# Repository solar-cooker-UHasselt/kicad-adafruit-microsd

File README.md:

# kicad-adafruit-microsd

A breakout board for a microSD card over SPI. It has a push-push socket with card
detect, an activity LED, a 3.3 V regulator for the card and a 74HC4050 level shifter so
it works with 3.3 V and 5 V boards. It is a KiCad 10 port of
[Adafruit's microSD breakout](https://github.com/adafruit/MicroSD-breakout-board),
originally drawn in Eagle.

In the [solar cooker](https://github.com/solar-cooker-UHasselt) testing station, the
firmware ([arduino-code](https://github.com/solar-cooker-UHasselt/arduino-code))
writes every measurement to CSV files on the card over SPI.

- [Board page](https://solar-cooker-uhasselt.github.io/kicad-adafruit-microsd/): 3D
  renders, drawings, schematic and board PDF, interactive BOM and the BOM CSV for
  Eurocircuits, rebuilt by CI on every push to `main`
- [PCB source](https://github.com/adafruit/MicroSD-breakout-board): Adafruit's Eagle
  files
- [Adafruit guide](https://learn.adafruit.com/adafruit-micro-sd-breakout-board-card-tutorial):
  pinout, wiring, card formatting and Arduino examples

## Installation

### Requirements

- [KiCad 10](https://www.kicad.org/download/), to open and edit the board
- [git](https://git-scm.com), to clone the repo
- Optional, for the checks: [just](https://just.systems)

### Clone

```bash
git clone https://github.com/solar-cooker-UHasselt/kicad-adafruit-microsd.git
```

Own symbols, footprints and 3D models are in `external/`, in the repo itself.

## Usage

Open `microSD.kicad_pro` in KiCad 10. The schematic and board open from there.

Before committing, run ERC and DRC, reports in `tmp/`:

```bash
just check
```

`just --list` shows the other recipes: PDFs, and the CI workflow run locally.

## Contributing

- Work on a branch and open a pull request to `main`. It merges once CI passes and a code
  owner (listed in [.github/CODEOWNERS](.github/CODEOWNERS)) approves it. `main`
  accepts no force pushes.
- CI runs ERC and DRC on every pull request, through the shared workflows in
  [kicad-ci](https://github.com/solar-cooker-UHasselt/kicad-ci). `just check` runs the
  same check locally. A push to `main` that changes more than Markdown also rebuilds
  the board page.
- Commits follow Conventional Commits, with one change per commit. Types, scopes and the
  ERC/DRC check are in
  [.agents/commit_conventions.md](.agents/commit_conventions.md).
- Changes to the board setup, CI or docs are made and tested in
  [kicad-adafruit-ds3231](https://github.com/solar-cooker-UHasselt/kicad-adafruit-ds3231)
  first, then copied here.

## Authors and acknowledgment

The board is Adafruit's design, by Limor Fried/Ladyada for Adafruit Industries
([PCB source](https://github.com/adafruit/MicroSD-breakout-board)). The KiCad 10 port is
by Lowie Van Vyve for the UHasselt solar cooker project.

Adafruit invests time and resources providing this open source design. Please support
Adafruit and open-source hardware by purchasing products from
[Adafruit](https://www.adafruit.com).

<details>
<summary>Adafruit's original README, included as its license asks</summary>

> **Adafruit MicroSD breakout board PCB**
>
> [Click here to purchase one from the Adafruit shop](http://www.adafruit.com/products/254)
>
> Not just a simple breakout board, this microSD adapter goes the extra mile - designed
> for ease of use.
>
> - Onboard 5v->3v regulator provides 150mA for power-hungry cards
> - 3v level shifting means you can use this with ease on either 3v or 5v systems
> - Uses a proper level shifting chip, not resistors: less problems, and faster
>   read/write access
> - Use 3 or 4 digital pins to read and write 2Gb+ of storage!
> - Activity LED lights up when the SD card is being read or written
> - Four #2 mounting holes
> - Push-push socket with card slightly over the edge of the PCB so its easy to insert
>   and remove
> - Comes with 0.1" header (unattached) so you can get it on a breadboard or use wires -
>   your choice
> - Tested and assembled here at the Adafruit factory
> - Works great with Arduino, with tons of example code and wiring diagrams
>
> This repo contains the PCB files for the Adafruit SPI Micro SD (transflash) breakout
> board
>
> **License**
>
> Adafruit invests time and resources providing this open source design, please support
> Adafruit and open-source hardware by purchasing products from
> [Adafruit](https://www.adafruit.com)!
>
> All text above must be included in any redistribution
>
> Designed by Limor Fried/Ladyada for Adafruit Industries. Creative Commons
> Attribution/Share-Alike, all text above must be included in any redistribution. See
> license.txt for additional information.

</details>

## License

[CC BY-SA 4.0](LICENSE). Adafruit's original design is licensed CC BY-SA 3.0, which
allows adaptations like this port under a later version with the same terms.

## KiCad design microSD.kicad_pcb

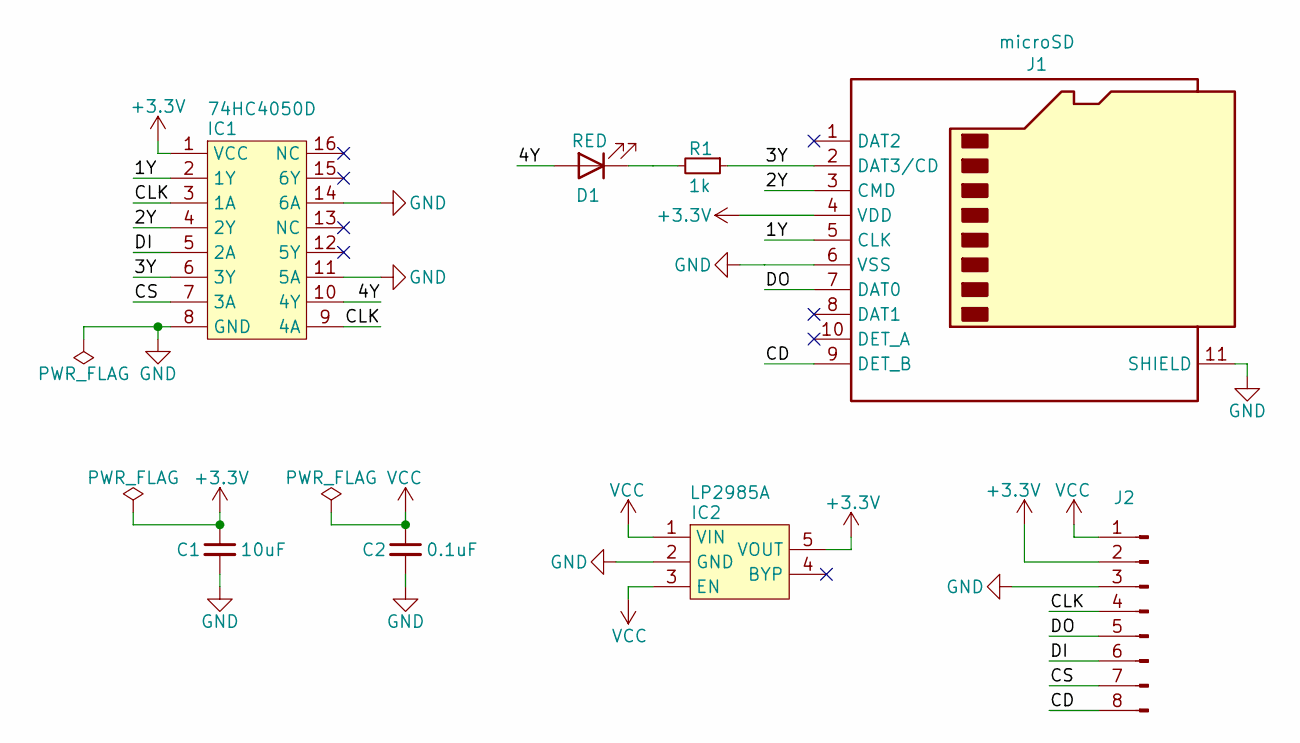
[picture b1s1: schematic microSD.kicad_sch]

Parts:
C1: 10uF; C_0805_2012Metric; MPN /
C2: 0.1uF; C_0805_2012Metric; MPN /
D1: RED; LED_0805_2012Metric; MPN 150080SS75000
IC1: 74HC4050D; SOIC-16_3.9x9.9mm_P1.27mm; MPN 74HC4050D
IC2: LP2985A; SOT-23-5; MPN LP2985A-33DBVR
J1: microSD; GCT_MEM2061-01-188-00-A_REVA; MPN MEM2061-01-188-00-A
J2: PinHeader_1x08_P2.54mm_Vertical; MPN TSW-108-23-G-S
R1: 1k; R_0805_2012Metric; MPN /

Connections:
+3.3V: C1.1, IC1.1 (VCC), IC2.5 (VOUT), J1.4 (VDD), J2.2
/1Y: IC1.2 (1Y), J1.5 (CLK)
/2Y: IC1.4 (2Y), J1.3 (CMD)
/3Y: IC1.6 (3Y), J1.2 (DAT3/CD), R1.1
/4Y: D1.2 (A), IC1.10 (4Y)
/CD: J1.9 (DET_B), J2.8
/CLK: IC1.3 (1A), IC1.9 (4A), J2.4
/CS: IC1.7 (3A), J2.7
/DI: IC1.5 (2A), J2.6
/DO: J1.7 (DAT0), J2.5
GND: C1.2, C2.2, IC1.8 (GND), IC1.11 (5A), IC1.14 (6A), IC2.2 (GND), J1.6 (VSS), J1.11 (SHIELD), J2.3
unnamed: D1.1 (K), R1.2
VCC: C2.1, IC2.1 (VIN), IC2.3 (EN), J2.1

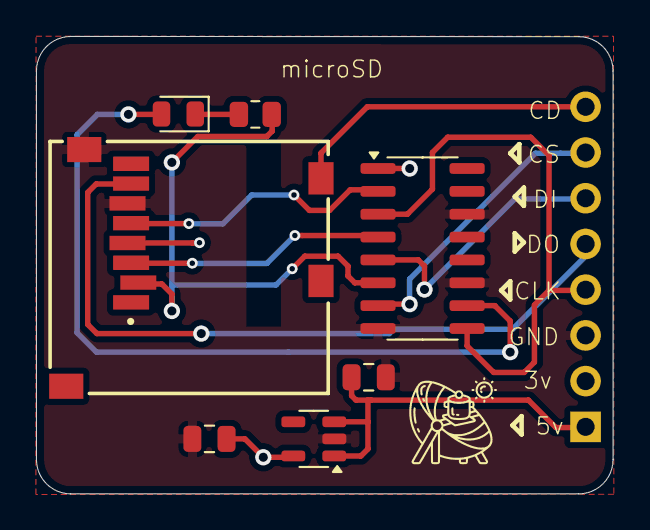
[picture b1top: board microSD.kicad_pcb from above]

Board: 2 copper layers, 32.0 x 25.4 mm, 8 parts (1 on the bottom side), 13 nets.

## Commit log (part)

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2024-03-05 .gitignore update
2024-03-05 blank KiCad project
2024-03-05 Eagle import
2024-03-06 added drawing sheet
2024-03-07 fully migrated to KiCad
2024-03-07 added info to generate BOM file
2024-03-07 removed Eagle import library
2024-03-14 minor fixes schematic and PCB
2024-04-01 silkscreen update
2024-04-01 silkscreen + BOM update
2024-04-01 production ready
2024-04-03 removed unused copper layers
2024-04-03 updated polygon
2024-04-03 changed copper finish + solder mask and silkscreen color update
2024-04-04 KiBot DRC check workflow
2024-04-05 project update
2024-05-02 changed pin header orientation
2024-05-21 external STEP folder rename
2024-06-10 BOM presets update
